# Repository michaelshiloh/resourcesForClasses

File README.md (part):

# General Resources for Classes

## Priorities (learned the hard way)

1. What is the minimum that you need to get done? Get that working first.
That way, if it's difficult you have more time to fix it, and if
it's impossible, you have more time to change your concept.  
1.1. If this is for a class, what's most of the grade?
1.1. If this is for yourself, what's the minimum you would need to feel proud?
1. In my experience, 
the mechanical things are the most difficult to get working, because usually
most students have the least amount of experience with this.
Get the mechanical parts work at least well enough before involving the
Arduino and programming.
1.1. If your robot is to be mobile, 
I would first get the mobility part working
1.1. If your robot has any other moving parts 
	(arms, tentacles, alien appendages, robot grippers) 
	I would try to get at least one of them working. 
1. The guiding principle is to do the things that you have the
least amount of experience with first And always leave the aesthetic stuff
until the very end. It doesn't matter if it looks like a jumble of junk, as
long as it works.  
1.1. One exception to the aesthetics is the wiring. As you've
probably discovered, a big mess of wires is very hard to debug, so spending
time to make the wires tidy can save you a lot of time later when things don't
work.

## Wisdom

1. MY GUIDING PRINCIPLES AFTER 20 YEARS OF PROGRAMMING
Medium
Alex Ewerlöf wrote an excellent article about his principles for working with software that I found could also apply to working on mechanical and electrical systems.

## Smoothing Readings from Noisy Sensors using Filters

1. Running average, built-in example in Arduino (File -> Examples -> Analog ->
Smoothing) [tutorial](https://www.arduino.cc/en/pmwiki.php?n=Tutorial/Smoothing)

1. [Another](https://maker.pro/arduino/tutorial/how-to-clean-up-noisy-sensor-data-with-a-moving-average-filter)
explanation of the running average filter

1. Great [discussion](https://www.megunolink.com/articles/coding/3-methods-filter-noisy-arduino-measurements/) and comparison
	of three smoothing methods: basic average, running average, and an
	exponential filter. The running average is the same as above. The
	exponential filter can be used by installing the *Megunolink* library
	(Sketch -> Include Library -> Manage Libraries, search for *Megunolink*) 

1. Many other filters are available through the library manager. I have not
	 tested these.

**Notes**
- While the examples above often refer to analog sensors, these methods
can be applied to all sensors (e.g. the ultrasonic distance measuring sensor)
- For beginners, I would recommend a basic average or a running average 
	- Basic average is faster to respond, but isn't quite as smooth as a running average.
	- In both cases, you will need to experiment with how many samples to take.  
		- A few samples responds quickly but won't be as smooth 
		- Many samples smooths well but won't respond quickly.  
	- You will have balance how much delay you can
tolerate vs. how smooth you need the result. Usually it's best to do this by
experimentation.

## Fabrication

1. Always design easy access for repair or modification. Never put items on
	 top of one another. Assume you will need easy access to each component.
	 Make access doors big so that you can easily put your hands in or bring
	 components out. Make holes for wires big enough that you can get the
	 connector through as well.
1. Make any enclosures at least twice as big as you think you'll need. Until
	 you're extremely experienced, you will underestimate how much room you'll
	 need and forget things like wires, which take up lots of space
1. Make wires longer than necessary, at least long enough that you can remove
	 a module and work on it comfortably (e.g. placing it face down on a
	 surface, not having to hold it at an uncomfortable angle)
1. Always use stranded wire between modules or between components and boards.
	 Solid wire can only be used when both ends are soldered to the same board.
1. Be consistent with colors: red for +5V (or whatever the dominant voltage
	 is), black wires for ground.
1. Don't have wires traverse empty space. Anchor wires to walls or other
	 support structures. Use zipties to bundle them neatly. 
1. Whenever possible, once you have finished the prototype transfer your
	 circuit from the solderless breadboard to a soldered board such as a
	 prototyping shield. Abolish all jumpers cables and instead solder
	 extensions as necessary. Use heat-shrink tubing on all solder joints to
	 prevent short circuits.

## Theory and critique
1. [Robotic Creatures](doc/roboticCreatures2010Ghedini.pdf)
1. [Catalog](doc/moma_catalogue_machine_art.pdf)
 from Machine Art exhibit, Museum of Modern Art, 1934 

### Art Critique: Examples and guides
1. [Beginner’s Guide to Writing an Art
   Critique](https://acousticpaint.wordpress.com/2018/07/31/beginners-guide-to-writing-an-art-critique/)
   Uses the foundational Feldman Method of art criticism.
   Somewhat beginner oriented. 
1. [How to: critique artwork like a
   pro](https://www.twistedtextiles.com/how-to-critique-artwork-like-a-pro/)
   As above
1. [Teaching Students to Critique](https://www.kennedy-center.org/education/resources-for-educators/classroom-resources/articles-and-how-tos/articles/educators/critique--feedback/teaching-students-to-critique/)
   As above
1. [How to Write an Art Critique: Examples &
   Strategies](https://custom-writing.org/blog/art-critique-writing)
   As above
1. [7 Art Critique Examples to Make You a Better Analyst
   (2025)](https://as.wiktoriaflorek.com/art-critique-examples/) describes 7
   different approaches to art criticism, all but one more advanced than the
   Feldman method. I found this the most useful because
   I could choose the approach that seems the most relevant to the situation
   and/or the artwork.
1. [Art Critique Example: The Persistence of Memory by Salvador
   Dali](https://hannahaafecak12.weebly.com/art-critique-example.html)
1. [Art Critique Example: The Weeping Woman by Pablo
   Picasso](https://16julianas.weebly.com/art-critique-example.html)

### Artist Statements
1. :
1. [8 Artist Statements We Love](https://www.theartleague.org/blog/2015/08/24/8-artist-statements-we-love/) this one starts with a Calvin and Hobbes cartoon so it's already a winner in my book
1. Reddit thread with [very useful advice from someone who covers art
   galleries](https://www.reddit.com/r/ContemporaryArt/comments/1emelpj/what_are_some_good_well_written_artist/)
1. Another Reddit thread with [useful
   advice](https://www.reddit.com/r/ContemporaryArt/comments/1dog1a4/the_artists_statement/)
1. [How To Write An Artist Statement, With
   Examples](https://www.stephaniescott.art/brushwork/2024/11/19/how-to-write-an-artist-statement)
   by someone who offers artist statement editing professionally
1. [Example Artist
   Statements](https://www.liverpoolmuseums.org.uk/example-artist-statements)
   from a museum so it must be good (I guess)
1. A whole bunch of [resources on writing artist
   statements](https://guides.ecuad.ca/professionalpractice/writing) with
   links to yet more examples
1. [Sample Artist Statements/Bios](https://www.gyst-ink.com/sample-artist-statements) from the resource above, because they
   seem really good

### Examples of well researched and well written papers about art
1. [Art of Interaction: A Theoretical Examination of Carsten Höller’s Test
   Site](https://www.tate.org.uk/research/tate-papers/15/art-of-interaction-a-theoretical-examination-of-carsten-holler-test-site)

## Inspiration: Artists, Movies, Projects, etc.

### Machine inspiration
- [DIY wire wrapping
- [Ghibli
	Clock](https://www.atlasobscura.com/places/the-giant-ghibli-clock-tokyo-japan)
	also [here](https://www.youtube.com/watch?v=R6nT8IEbaJM)
  machine](https://www.youtube.com/watch?v=3QL1QaIwMwk&t=482s)
- [Astronomical Clock Strasbourg
- [Fortnum & Mason store clock](https://www.youtube.com/watch?v=T7dWeTyexEg)
	Cathedral](https://www.youtube.com/watch?v=lKgZB3P45Kw)
- Series of 15 videos on [Mechanical
	Principles](https://www.youtube.com/watch?v=-42Z-_Kq0QU&list=PLq_UHnXWA4jI_gSAW9rvOr-I5Spqi3i_H)

1.  Drawing Machines
	1. [1](https://www.raspberrypi.org/blog/hanging-wall-plotter/)    
	1. [2](https://www.youtube.com/watch?v=T0jwdrgVBBc)    
	1. [3](http://www.homofaciens.de/technics-machines-v-plotter_en.htm)  
	1. [4](https://www.pinterest.com/pin/516014069788859472/)  
	1. [5](http://www.instructables.com/id/CNC-HANGING-PLOTTER/)  
	1. [6](http://patriciogonzalezvivo.com/2014/vPlotter/)  
	1. [7](http://www.instructables.com/id/Polargraph-Drawing-Machine/)  
	1. [8](https://www.thingiverse.com/thing:12557)  
	1. [9](https://www.thingiverse.com/thing:12403)  
	1. [10](http://makerblock.com/2013/03/a-study-of-drawing-robot-pen-holders-and-design-considerations/)  
	1. [11](https://www.kickstarter.com/projects/1765367532/duograph-drawing-machine?ref=nav_search)  
	1. [12](http://www.thisiscolossal.com/2016/03/cycloid-drawing-machine/)  
	1. The Machine As Artist, an
		 [Introduction](doc/theMachineAsArtistIntroduction.pdf)
  
1. Marble Machines
	1. [1](https://www.youtube.com/user/denha)  
	1. [2](https://tinkerlog.com/)  
	1. [3](https://www.youtube.com/watch?v=3OGyLHu24rk)

1. Didi Vardi's Wonderful Mechamisms
	1. [Binary Counter with old computer parts](media/binaryCounterDidiVardi.wmv)
	1. [Machine Animating late 19th century and early 20th century hand
		 tools](media/oldToolsMachineDidiVardi.wmv)

1. Musical Machines
	1. Carlos Guedes' wonderful [Phobos, Orquestra Robótica
	Disfuncional[(https://vimeo.com/235763130)
	4. Sudhu Tewari's [Yasmin Electro Mechanical 
	Sequencer](https://www.youtube.com/watch?v=MjNB3nKPMb8)
	1. Solenoid tapping wine glasses by [Lilliana Matta](https://vimeo.com/202356514) password
		 2424

1. List of [inspirational movies](http://eat.cca.edu) collected by [Barney
Haynes](http://www.ultrafuzz.net/) (also
[here](https://vimeo.com/barneyhaynes)) and shown at his Interface classes. In
particular

1. Inspirational videos collected by [J.D.
Zamfirescu](https://github.com/zamfi)  
	1. Basic robots  
		1. [Tree-climbing robot](http://www.youtube.com/watch?v=zkpH1BjD6Wc)  
		1. [Self-balancing robot](http://www.youtube.com/watch?v=Tw9Jr-SPL0Y)  
		1. [Insect robot](http://www.youtube.com/watch?v=tOsNXg2vAd4#t=120)  
		1. [Treadbot](http://www.youtube.com/watch?v=YblSltHDbIU)  
		1. [Velociraptor robot](http://www.youtube.com/watch?v=lPEg83vF_Tw)  
	1. Installations  
		1. [The Bay Lights](http://thebaylights.org/)  
		1. [Murmur Wall](http://www.future-cities-lab.net/projects/#/murmurwall/)  
		1. [Floating Couch](http://vimeo.com/72826106)  
		1. [Wooden Segment Mirror](https://www.youtube.com/watch?v=BZysu9QcceM#t=36)  
		1. [Generative design](https://www.youtube.com/watch?v=pNkz8wEJljc)  
	1. Art & Music bots  
		1. [Textile weaving](https://vimeo.com/71044541)  
		1. [ReacTable](https://www.youtube.com/user/marcosalonso)  
		1. [Projection mapping](https://www.youtube.com/watch?v=czuhNcNU6qU)  
		1. [Laser harp](http://www.youtube.com/watch?v=sLVXmsbVwUs#t=20)  
		1. [Cubli: Floating Cube](https://www.youtube.com/watch?v=n_6p-1J551Y)  
		1. [Arc-o-matic](http://vimeo.com/57082262#at=130)  
		1. [Robo Faber](http://vimeo.com/78771257)  
		1. [Eggbot](https://www.youtube.com/watch?v=w4cdbV2oaEc)  
	1. Drink-makers  
		1. [Textspresso](http://www.youtube.com/watch?v=kx9D74t7GD8#t=89)  
		1. [The Inebriator](http://www.youtube.com/watch?v=WqY7fchs7H0)  
	1. Computer Numerical Control (CNC)  
		1. [Shapoko / tinyg](http://www.youtube.com/watch?v=pCC1GXnYfFI#t=11)  
		1. [Makerbot Replicator](http://www.youtube.com/watch?v=NAbiAzYhTOQ)  
	1. Vacuuming  
		1. [Roomba](https://www.youtube.com/watch?v=0DNkbZvVYvc)  

2. [Golan Levin: Art that looks back at
you](https://www.youtube.com/watch?v=1G0MzlfMPuM)

3. [Drawdio](https://www.youtube.com/watch?v=PV_w38ldZaE)

4. Other Projects  
	1. Alex Markova's [fortune wheel](http://intro17fall.nyuad.im/2017/10/09/homework-due-october-9/)  
	1. Claire Neel's [reactive eye](https://youtu.be/lYERKTf5YtI)  
	1. Ji Young Kim's [map and national anthems](https://youtu.be/JknAOpjAkmQ)
	1. May Baho's [campfire](http://intro17fall.nyuad.im/wp-content/uploads/2017/12/IMG_2544.jpg)  

### Solderless Breadboards

1. [How to Use a Breadboard](https://learn.sparkfun.com/tutorials/how-to-use-a-breadboard) tutorial by Sparkfun
1. [Setting Up a Breadboard](https://itp.nyu.edu/physcomp/labs/labs-electronics/breadboard/) lab at NYU ITP

### Basic Electronics

1. [Basic Electronics](https://learn.sparkfun.com/tutorials/voltage-current-resistance-and-ohms-law) tutorial by Sparkfun
1. [Electricity: the Basics](https://itp.nyu.edu/physcomp/lessons/electronics/electricity-the-basics/) tutorial at NYU ITP

### Data Visualization Examples

1. [Ben Fry](http://benfry.com/allstreets/)

2. [Aaron Koblin](http://www.aaronkoblin.com/project/flight-patterns/)

3. Jer Thorp

	3.1. [Just
Landed](http://blog.blprnt.com/blog/blprnt/just-landed-processing-twitter-metacarta-hidden-data)

	3.2. [another](http://nytlabs.com/projects/cascade.html)

	3.3. [nytimes top coverage and
connections](https://www.flickr.com/photos/blprnt/sets/72157614008027965/with/3288898519/)

4. [Nicholas Feltron](http://feltron.com/FAR14.html)

### Mechanical or Primarily Mechanical

1. [Survival Research Labs](http://www.srl.org) Machine or industrial art

2. [Matt Heckert](http://www.mattheckert.com/)
Machine and kinetic art, machine sound art, and creator of many early SRL
machines

3. [Carl Pisaturo](http://carlpisaturo.com/index.html)
Artist, master machinist, and inventor, Carl documents his process in detail
for great learning opportunities. Great examples of complex motions via cables

4. [North Pitney](http://www.northpitney.com/)
North Pitney’s amazing [reconfigurable maze](http://www.northpitney.com/works/maze/maze.html) is one of my favorite examples of kinetic art.

5. Arthur Ganson
makes amazing sculptures using wire gears and mechanisms
[Making wire gears](http://www.youtube.com/watch?v=f0UNz-ayzrE)
Sample piece: [Meditation #1](http://www.youtube.com/watch?v=kY2Df78faiE)
Search youTube for many other videos of his work

6. Daniel Rozinin
[Wooden
mirror](http://www.designboom.com/weblog/read.php?CATEGORY_PK=&TOPIC_PK=2897) 
in which over 800 small blocks of wood
are individually rotated slightly to display an image of what the camera
captures

7. [Theo Jansen](http://www.strandbeest.com/)
Theo Jansen creates new forms of life using plastic tubing as the basic
building material. Wind is their "food", and their "stomach" is made of recycled
plastic bottles.
Theo’s [The art of creating
creatures](http://www.youtube.com/watch?v=b694exl_oZo) 
presentation at TED in 2006 includes
a wonderful video of his work and a live demonstration of portions of his
mechanisms. Search youTube for many other videos of his work

8. [Del’s Beautiful New Wooden
Machine](http://www.youtube.com/watch?v=u7ziwuIpnVY)
An intricate hand-cranked machine demonstrating many types of simple
mechanisms: cranks, gears, chains, sprockets, offset gears to change speed,
escapements, conversion of rotary motion to linear motion. Thanks to Tristan
for bringing this to my attention.

## Basic Arduino Resources from Arduino

1. Getting Started with Arduino / Genuino Uno
    [tutorial](https://www.arduino.cc/en/Guide/ArduinoUno)

1. Blink [tutorial](http://arduino.cc/en/Tutorial/Blink)

1. DigitalReadSerial [tutorial](http://arduino.cc/en/Tutorial/DigitalReadSerial)

1. AnalogReadSerial [tutorial](http://arduino.cc/en/Tutorial/AnalogReadSerial)

2. Fade [tutorial](http://arduino.cc/en/Tutorial/Fade)
shows how to use the `analogWrite()` function

## Basic Arduino Resources from Other Sources

1. Arduino basics: Intro through Lesson 3 of Adafruit's Arduino [tutorial](http://www.ladyada.net/learn/arduino/index.html)

1. [Arduino in a Nutshell](http://hci.rwth-aachen.de/arduino)

1. Photoresistor
[Instructables](http://www.instructables.com/id/How-to-Use-a-Light-Dependent-Resistor-LDR/)

## Sparkfun Inventor's Kit Resources

1. [Introduction](https://learn.sparkfun.com/tutorials/sik-experiment-guide-for-arduino---v32/introduction-sik-arduino-uno)
to the Sparkfun Inventor's Kit for Arduino Experimenter's Guide

1. [Experiment 1: Blinking an LED](
https://learn.sparkfun.com/tutorials/sik-experiment-guide-for-arduino---v32/experiment-1-blinking-an-led)
in the Sparkfun Inventor's Kit for Arduino Experimenter's Guide

1. [Experiment 2: Reading a
Potentiometer](https://learn.sparkfun.com/tutorials/sik-experiment-guide-for-arduino---v32/experiment-2-reading-a-potentiometer)
in the Sparkfun Inventor's Kit for Arduino Experimenter's Guide

## Blink Without Delay Resources

1. [Tutorial](https://www.arduino.cc/en/Tutorial/BlinkWithoutDelay)
to Blink Without Delay on the official Arduino website

1. [Another](https://www.baldengineer.com/millis-tutorial.html) 
explanation of Blink Without Delay recommended by a student

1. The same student recommends that in order to understand Blink Without
Delay, it is wise to first understand
[millis()](https://www.arduino.cc/en/Reference/Millis)

1. Very detailed line-by-line
[explanation](https://www.baldengineer.com/blink-without-delay-explained.html)
of Blink Without Delay, with links
to explanations of related concepts every step of the way.

2. A detailed
[explanation](https://programmingelectronics.com/tutorial-16-blink-an-led-without-using-the-delay-function-old-version/) of Blink Without Delay. 
I don't like the way he does the circuit, but his explanation is good.

## Arduino Multitasking Resources

1. Excellent Adafruit Multitasking
[Tutorial](https://learn.adafruit.com/multi-tasking-the-arduino-part-1?view=all)
(highly recommended)

1. Play a melody and blink an LED
without using `delay()`:
[toneMelodyAndBlinkWithoutDelay](https://github.com/michaelshiloh/toneMelodyAndBlinkWithoutDelay)

1. Flicker (i.e simulate a candle) multiple LEDs
without using `delay()`:
[flickerMultipleNoDelay](https://github.com/michaelshiloh/resourcesForClasses/blob/master/src/arduinoSketches/flickerMultipleNoDelay/flickerMultipleNoDelay.ino)

## State, state machines, and state change detection (edge detection)

1. [State Change Detection](https://www.arduino.cc/en/Tutorial/StateChangeDetection)

1. A formal State Machine is called a *Finite State Machine* (FSM). Although
	 you can often get away with being less formal, here is a nice
	 [tutorial](https://www.instructables.com/Finite-State-Machine-on-an-Arduino/)
	 on FSMs

2. Adafruit 
	[tutorial](http://www.ladyada.net/learn/arduino/lesson5.html)

3. Another 
	[edge detection tutorial](https://programmingelectronics.com/tutorial-18-state-change-detection-and-the-modulo-operator-old-version/)

## Arduino Tone Resources

1. Decent explanation
[here](https://programmingelectronics.com/an-easy-way-to-make-noise-with-arduino-using-tone/)

2. Using switches to control the tone
[here](http://arduino-tutorials.eu/creating-sounds-with-arduino-buzzer)

## Arduino Sensors Resources

1. Adafruit [guide](http://www.ladyada.net/learn/sensors/) to sensors

## Shift Register resources

1. Adafruit Shift Register
[tutorial](https://learn.adafruit.com/adafruit-arduino-lesson-4-eight-leds/the-74hc595-shift-register)

1. Arduino Shift Register
[tutorial](https://www.arduino.cc/en/Tutorial/ShiftOut)

2. Electronics Tutorials
Shift Register
[tutorial](https://www.electronics-tutorials.ws/sequential/seq_5.html)

1. Sparkfun 
Shift Register
[tutorial](https://learn.sparkfun.com/tutorials/shift-registers)

## Communication resources

1. Sparkfun Serial Communication tutorial
[here](https://learn.sparkfun.com/tutorials/serial-communication)

## Miscellaneous Electronic resources

1. Sparkfun 
Logic Level 
[tutorial](https://learn.sparkfun.com/tutorials/logic-levels)

## Mechatronic Resources

1. [Walking
	 boots](https://www.mutualart.com/Artwork/THESE-BOOTS-ARE-MADE-FOR-WALKING/8DF4DB74D0B36CA0)

1. YouTube [playlist](https://www.youtube.com/playlist?list=PLLFpXNanTP9X6lHrX9qoJroqGAQRDDvV9)
of antique (and ancient) counting and calculating devices with a huge variety of mechanisms 

1. Ken Shirriff
	 [details](https://www.righto.com/2023/01/inside-globus-ink-mechanical-navigation.html)
the intricate mechanical systems of the Globus INK – a gorgeous navigation system for soviet spacecraft. It features a rotating globe inside a metal housing, and let Soyuz cosmonauts see their position above Earth.

1. Simple [descriptions](http://www.mechanical-toys.com/mechanisums.htm) of
the 6 basic mechanisms

1. [Table of Mechanicks
	 [sic]](media/Table_of_Mechanicks_Cyclopaedia_Volume_2.jpg)

1. Great book describing how to build [Mechanisms](doc/machinations-mechanisms.pdf)

1. How to build a [Crank and
	 Slider](https://www.wikihow.com/Build-a-Crank-and-Slider-Mechanism) 
	 mechanism

1. [Gear generator](http://www.geargenerator.com)

1. Pages 272-281 in "Physical Computing: Sensing and Controlling the
Physical World with Computers" by Igoe/O'Sullivan

1. [How To Design And Make Automata](doc/howToDesignAndMakeAutomata_RobertAdams.pdf) by Robert Adams

1. [How To Design And Make Simple Automata](doc/howToDesignAndMakeSimpleAutomata_RobertAdams.pdf) by Robert Adams (I think this is a different version of the same book above)

1. Different shaped cams provide [different types of reciprocating motion](https://static.fratello.com/2021/08/camupdate1.gif)

1. A nice [overview](https://makezine.com/projects/make-your-own-gears/) of
making your own gears. Don't worry about the specifics (Inkscape etc.) 
but get the general concept which can be achieved in many different 
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
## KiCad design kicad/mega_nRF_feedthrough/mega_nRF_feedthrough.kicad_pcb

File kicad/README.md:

Some PCBs I have designed to help with my classes and other projects:
- ArduinoShieldHobbyRCAndMotorControl: Holes for 6 wires to connect
  to an L298 (or similary) dual H-bridge motor driver, and six connectors
  suitable for a hobby RC receiver. 
  Used in [Performing
  Robots](https://github.com/michaelshiloh/PerformingRobots)
  but could be useful to
  anyone connecting an Arduino Uno to a hobby RC receiver or an L298 dual
  H-bridge motor driver.
- IC_sockets/16PinSocketAPC: breakout board for a 14 pin DIP, with silkscreen
  markings aimed at making at Atari Punk Console. I'll add a link to the full
  instructions when I find them.
- nRF_servo_Mega: Arduino Mega shield for mounting nRF24L01 and attaching six
  servo motors or NeoPixels strings with separate power supply
  Used in [Performing
  Robots](https://github.com/michaelshiloh/PerformingRobots).
  but could be useful to
  anyone connecting an Arduino Mega to an nRF24L01
  or servo motors/NeoPixel strings.
- l298Interface: rather than using horrible jumper cables, this board fits
  directly to the 6 control pins on an L298 dual H-bridge motor driver and
  provides holes for soldering wires to the
  ArduinoShieldHobbyRCAndMotorControl above. Also includes a 3 position ground
  tie point to avoid having to jam 2 wires into one of the screw terminals.
  Used in [Performing
  Robots](https://github.com/michaelshiloh/PerformingRobots) but could be
  generically useful.
- Arduino_Shield_RC_Controller: Obsolete. Do not use.
- Arduino_Shield_RC_Controller_v2: Wireless remote control panel using the
  nRF24L01.
  Used in [Performing
  Robots](https://github.com/michaelshiloh/PerformingRobots)
  but could be useful to
  anyone wanting a wireless remote control panel using an nRF24L01.
- motorMatrixAdapter: starting point for my matrix-of-motors project
- ArduinoShieldServoMotors: Arduino Uno shield for 9 servo motors or NeoPixel
  strands with separate power supply.
  Used in [Machine 
  Lab](https://github.com/michaelshiloh/MachineLab) 
  but could be useful to
  anyone connecting servo motors to an Arduino Uno
- nRFControlPanel: Obsolete. Do not use.

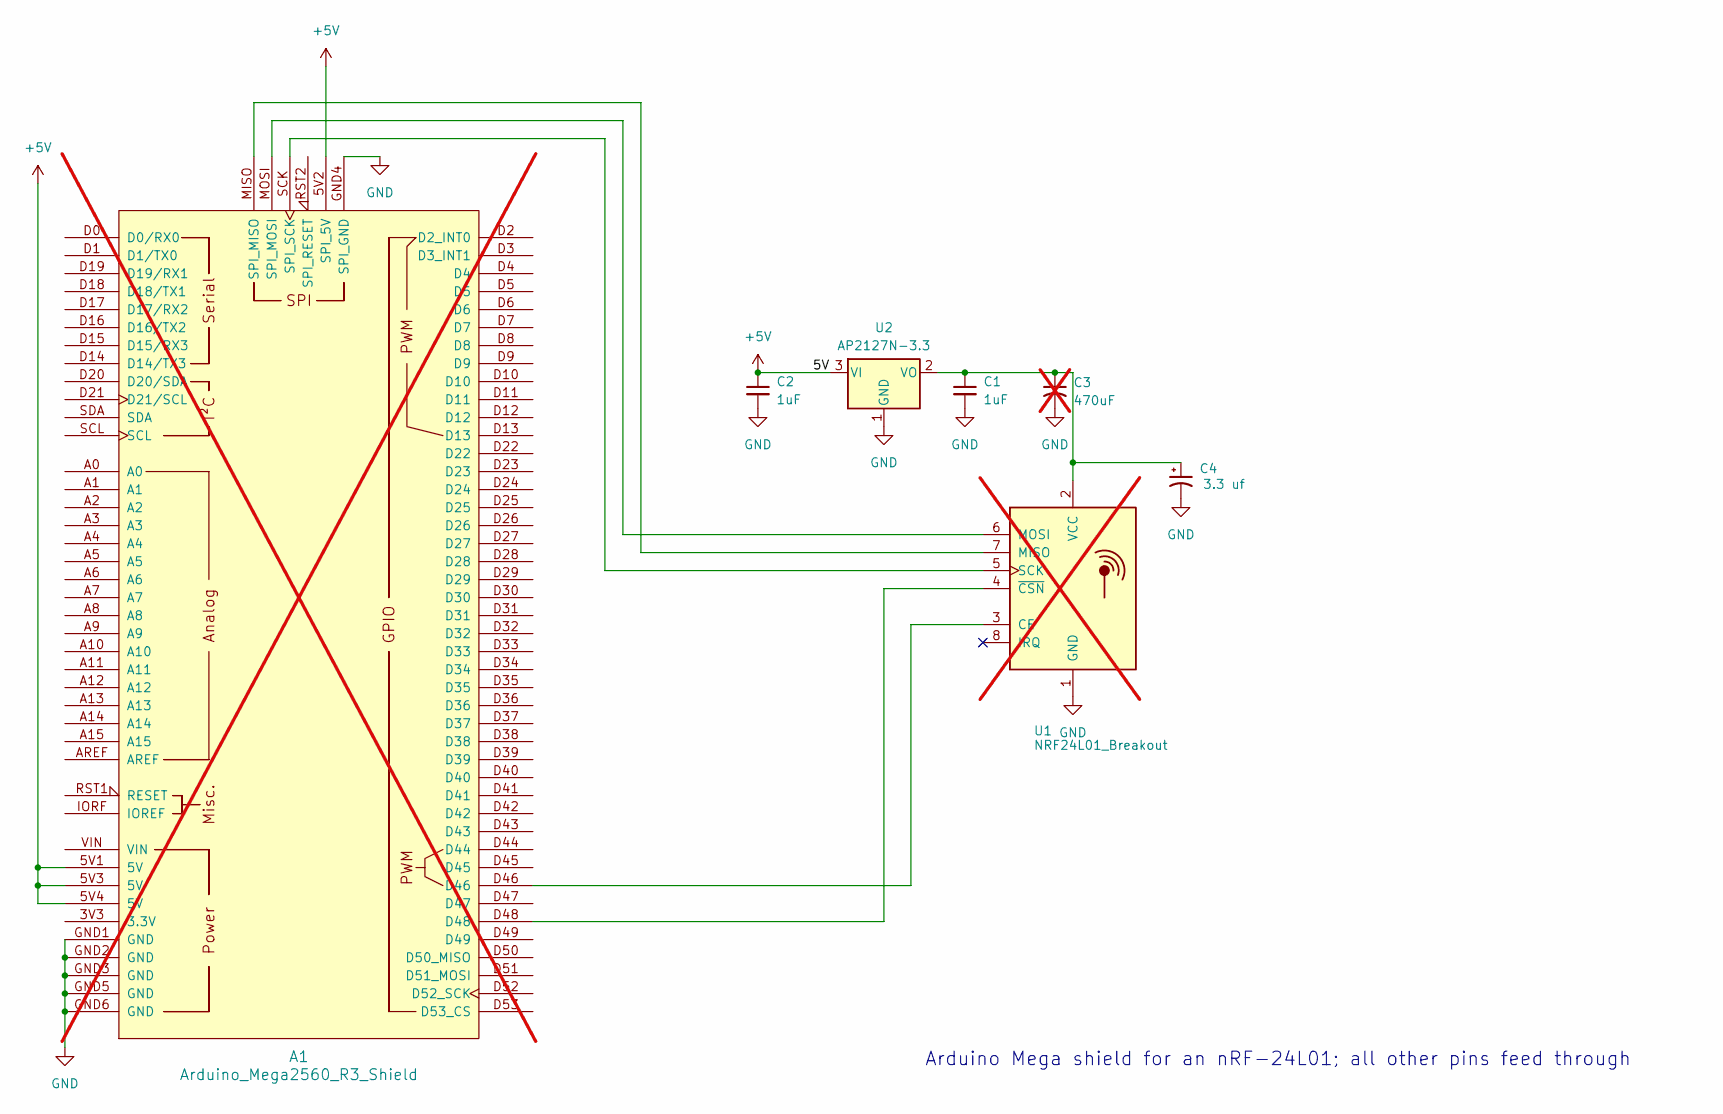
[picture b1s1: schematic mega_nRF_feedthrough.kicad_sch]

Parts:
A1: Arduino_Mega2560_R3_Shield; not fitted
C1: 1uF; C_0603_1608Metric; LCSC part # C1592
C2: 1uF; C_0603_1608Metric; LCSC Part # C1592
C3: 470uF; CP_Radial_D8.0mm_P3.50mm; not fitted
C4: 3.3 uf; CP_EIA-3216-18_Kemet-A_HandSolder; LCSC Part # C7184
U1: NRF24L01_Breakout; nRF24L01_Breakout; not fitted
U2: AP2127N-3.3; SOT-23

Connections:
+5V: A1.5V1 (5V), A1.5V2 (SPI_5V), A1.5V3 (5V), A1.5V4 (5V), C2.1, U2.3 (VI)
GND: A1.GND1 (GND), A1.GND2 (GND), A1.GND3 (GND), A1.GND4 (SPI_GND), A1.GND5 (GND), A1.GND6 (GND), C1.2, C2.2, C3.2, C4.2, U1.1 (GND), U2.1 (GND)
unnamed: A1.MISO (SPI_MISO), U1.7 (MISO)
unnamed: A1.MOSI (SPI_MOSI), U1.6 (MOSI)
unnamed: A1.SCK (SPI_SCK), U1.5 (SCK)
unnamed: A1.D46, U1.3 (CE)
unnamed: C1.1, C3.1, C4.1, U1.2 (VCC), U2.2 (VO)
unnamed: A1.D48, U1.4 (~CSN)

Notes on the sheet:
Arduino Mega shield for an nRF-24L01; all other pins feed through

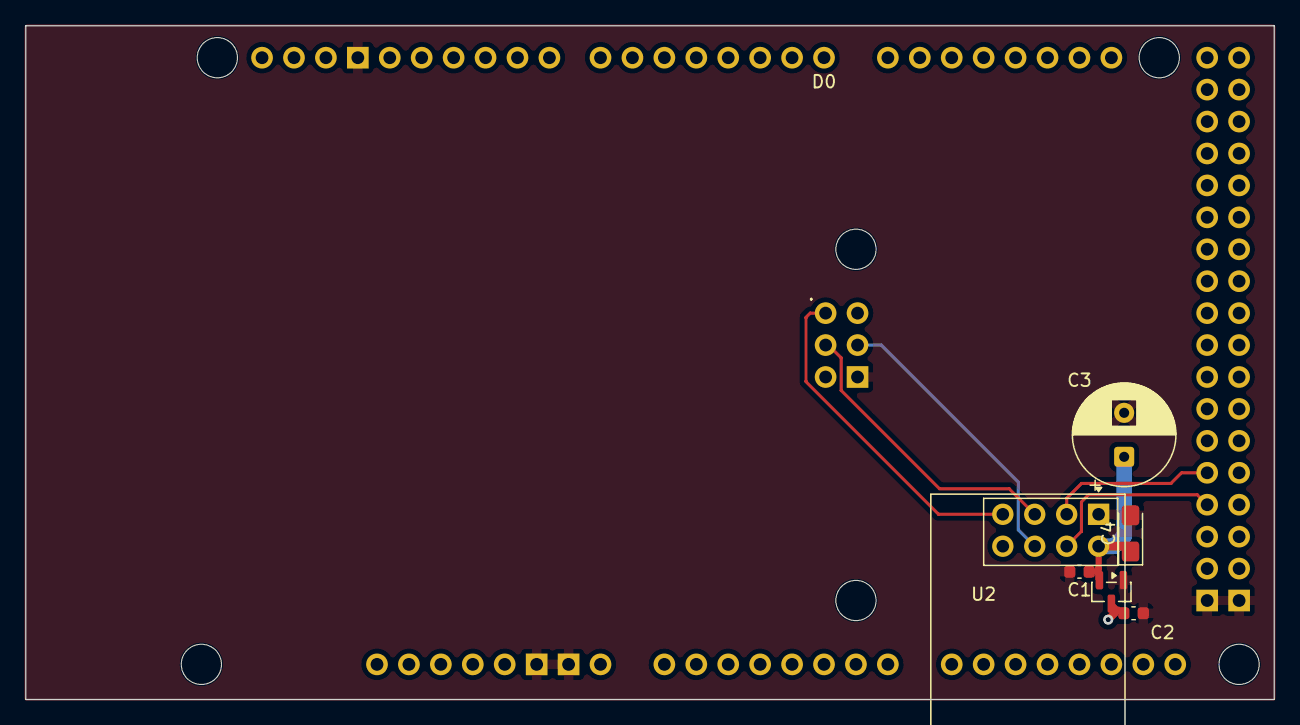
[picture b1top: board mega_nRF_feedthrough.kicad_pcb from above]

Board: 2 copper layers, 99.3 x 53.6 mm, 7 parts (0 on the bottom side), 8 nets.

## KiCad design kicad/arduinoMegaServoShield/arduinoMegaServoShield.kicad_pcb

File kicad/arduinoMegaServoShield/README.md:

### nRF_Servo_Mega

![](documentation/arduinoMegaServoShield.jpg
[PDF schematic](documentation/arduinoMegaServoShield.pdf)

Simple Arduino Mega shield which provides as many connections to servo motors
or other 3-pin devices (such as NeoPixels) with an independent +V supply

Be aware of pins which might be used for other purposes

Music Maker Shield

(why is the first column labled SPI?)
| SPI Signal Name | Description | Arduino Mega Pin |
| --- | --- | --- |
| MCS | VS1053 chip select pin | 7 |
| DCS | VS1053 data select pin | 6 |
| CCS | SD Card chip select pin | 4 |
| DREQ | VS1053 data request interrupt pin | 3 |

SPI

| SPI Signal Name | Arduino Mega Pin |
| --- | --- |
| CIPO | 50 |
| COPI | 51 |
| SCK | 52 |
| CS | 53 |

I2C (also known as Wire or 2Wire)

| I2C Signal Name | Arduino Mega Pin |
| --- | --- |
| SDA | 20 |
| SCL | 21 |

Serial 

| Serial Signal Name | Arduino Mega Pin |
| --- | --- |
| RX | 0 |
| TX | 1 |

#### Revisions

#### Assembly instructions
##### Assembly order
1. servo pins
1. Stacking headers
1. Screw terminal
1. ICSP header
1. 470 uFD caps

(Note that the order of the instructions and video below are slightly
different - I don't think it makes much of a difference.)

##### Assembly instructions
nRF Servo Mega Shield [video](https://youtu.be/EMkqwKK7xOQ)

1. Prepare many sets of header pins, each with 3 positions. 

    Insert into positions
   D16-D21.
   Solder one pin, straighten, and
   then solder the rest of the pins. You may find it easier to do one header
   at a time instead of trying to do all 6 at once like I did.
    
1. From the bag of feed-through headers, remove six 5 position headers and one
   10 position header. Return the rest to the bag.
    Solder one pin, straighten, then solder the rest. It is very important to
    get these to line up properly so don't solder the rest of the pins until
    the header is straight.
1. Install the feed through header that is two rows of 3 pins. **Note that
   this goes in the opposite direction i.e. the pins face up and the socket
   faces down**. Solder and straighten.
1. Install the 470 uFD electrolytic capacitor. 
    Note that this component **is polarized** so you have to install it in
    the right direction. The grey stripe must go into the hole with the white
    semicircle.
   Cut the excess leads right down to the solder. Discard the cut of portion
   so that it doesn't cause a short circuit
1. Install the screw terminal. Make sure that the openings face the edge of
   the board. Solder. These pins are quite thick and the hole is quite big, so
   keep feeding solder until the hole fills up.

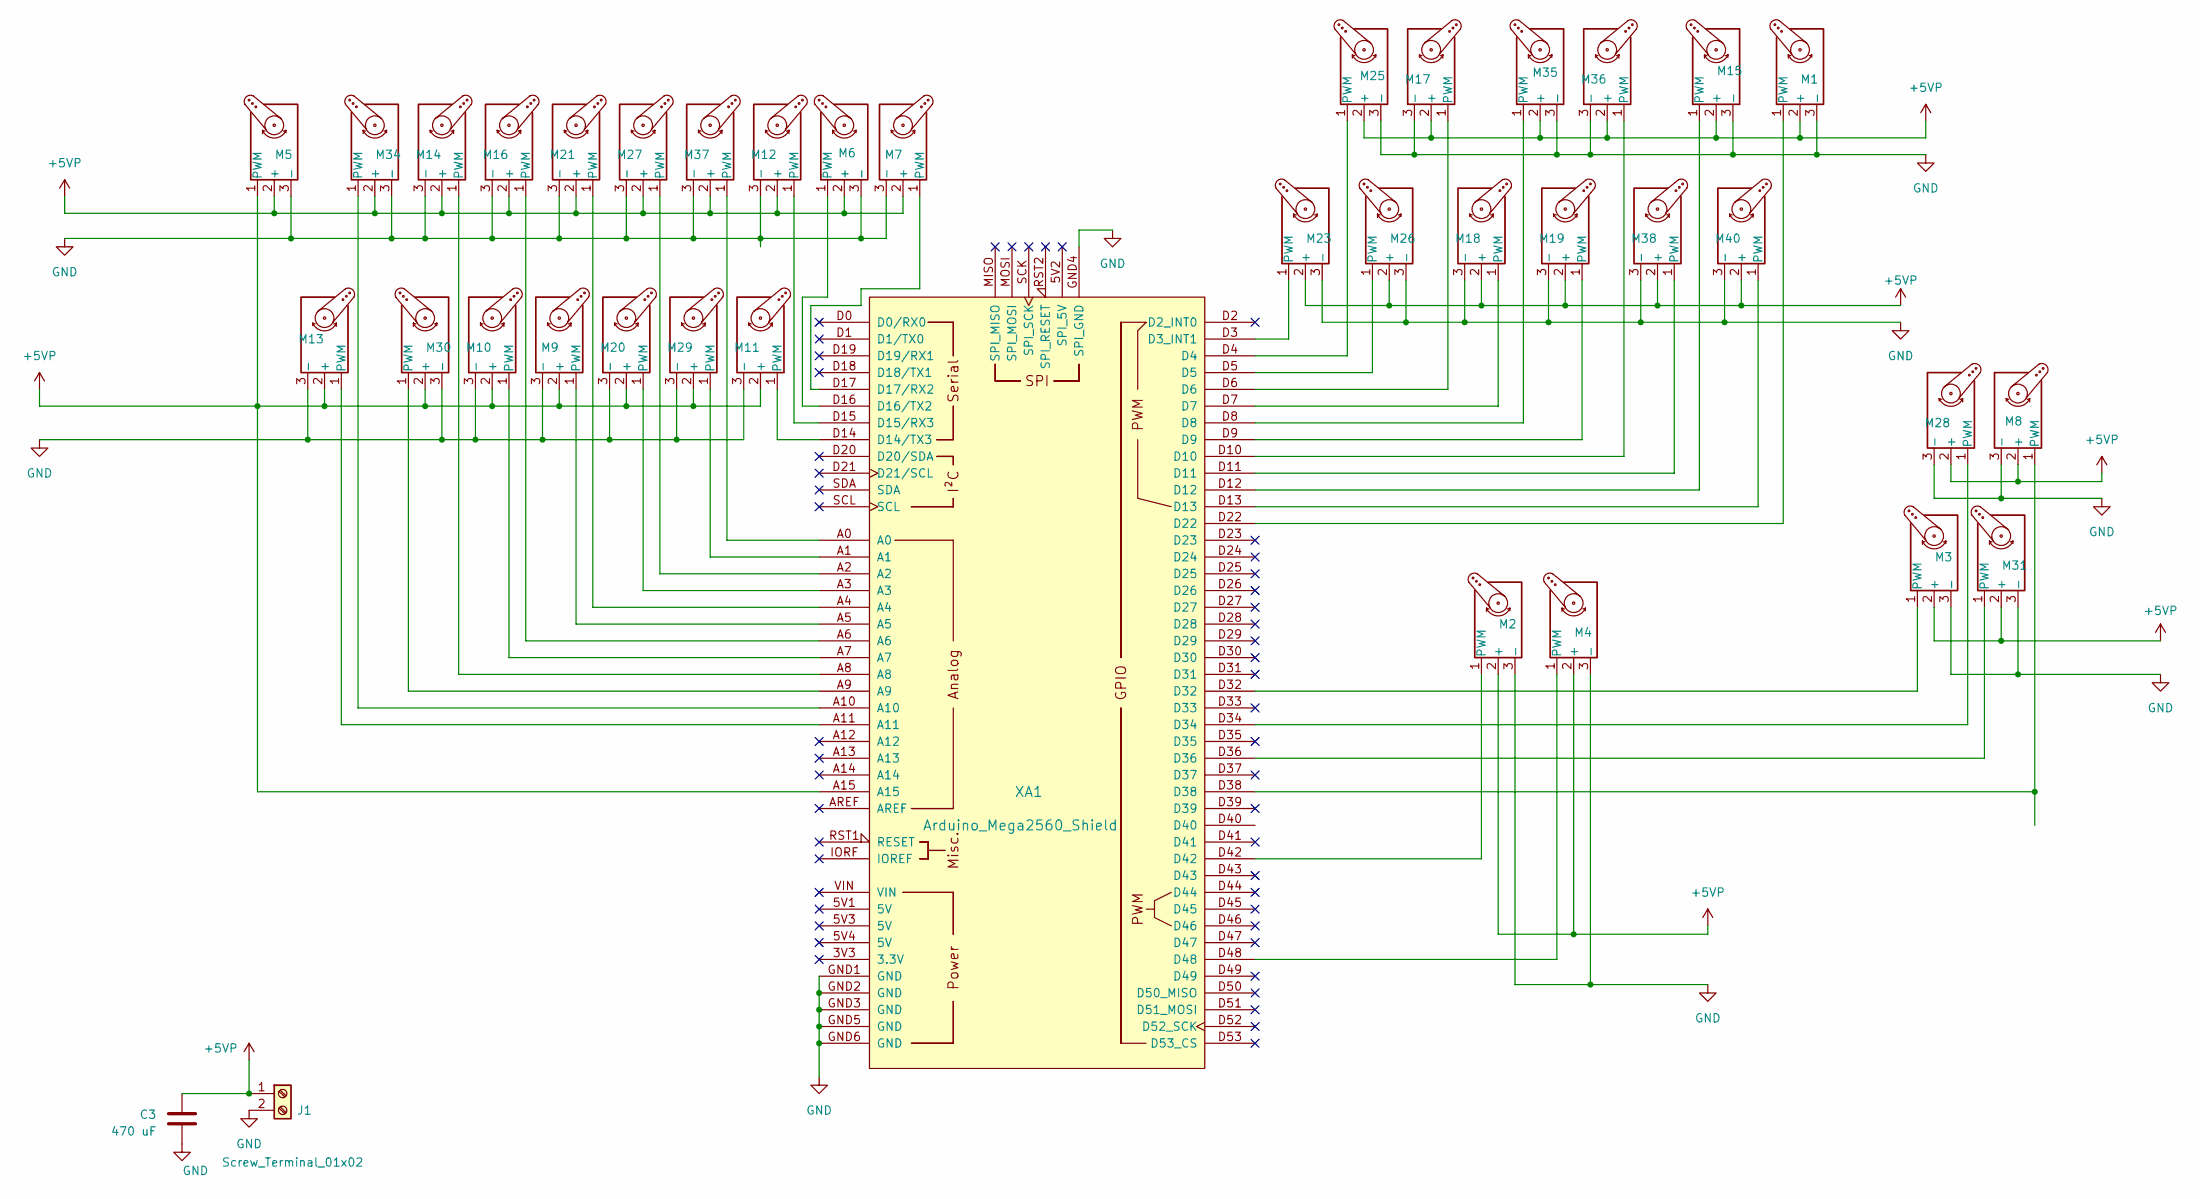
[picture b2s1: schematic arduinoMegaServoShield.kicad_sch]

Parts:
C3: 470 uF; CP_Radial_D10.0mm_P5.00mm
J1: Screw_Terminal_01x02; TerminalBlock_bornier-2_P5.08mm
M1, M2, M3, M4, M5, M6, M7, M8, M9, M10, M11, M12, M13, M14, M15, M16, M17, M18, M19, M20, M21, M23, M25, M26, M27, M28, M29, M30, M31, M34, M35, M36, M37, M38, M40: Motor_Servo; PinHeader_1x03_P2.54mm_Vertical
XA1: Arduino_Mega2560_Shield

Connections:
+5VP: C3.1, J1.1, M1.2 (+), M2.2 (+), M3.2 (+), M4.2 (+), M5.1 (PWM), M5.2 (+), M6.2 (+), M7.2 (+), M8.2 (+), M9.2 (+), M10.2 (+), M11.2 (+), M12.2 (+), M13.2 (+), M14.2 (+), M15.2 (+), M16.2 (+), M17.2 (+), M18.2 (+), M19.2 (+), M20.2 (+), M21.2 (+), M23.2 (+), M25.2 (+), M26.2 (+), M27.2 (+), M28.2 (+), M29.2 (+), M30.2 (+), M31.2 (+), M34.2 (+), M35.2 (+), M36.2 (+), M37.2 (+), M38.2 (+), M40.2 (+), XA1.A15
GND: C3.2, J1.2, M1.3 (-), M2.3 (-), M3.3 (-), M4.3 (-), M5.3 (-), M6.3 (-), M7.3 (-), M8.3 (-), M9.3 (-), M10.3 (-), M11.3 (-), M12.3 (-), M13.3 (-), M14.3 (-), M15.3 (-), M16.3 (-), M17.3 (-), M18.3 (-), M19.3 (-), M20.3 (-), M21.3 (-), M23.3 (-), M25.3 (-), M26.3 (-), M27.3 (-), M28.3 (-), M29.3 (-), M30.3 (-), M31.3 (-), M34.3 (-), M35.3 (-), M36.3 (-), M37.3 (-), M38.3 (-), M40.3 (-), XA1.GND1 (GND), XA1.GND2 (GND), XA1.GND3 (GND), XA1.GND4 (SPI_GND), XA1.GND5 (GND), XA1.GND6 (GND)
unnamed: M1.1 (PWM), XA1.D22
unnamed: M2.1 (PWM), XA1.D42
unnamed: M3.1 (PWM), XA1.D32
unnamed: M4.1 (PWM), XA1.D48
unnamed: M6.1 (PWM), XA1.D16 (D16/TX2)
unnamed: M7.1 (PWM), XA1.D17 (D17/RX2)
unnamed: M8.1 (PWM), XA1.D38
unnamed: M9.1 (PWM), XA1.A5
unnamed: M10.1 (PWM), XA1.A7
unnamed: M11.1 (PWM), XA1.D14 (D14/TX3)
unnamed: M12.1 (PWM), XA1.D15 (D15/RX3)
unnamed: M13.1 (PWM), XA1.A11
unnamed: M14.1 (PWM), XA1.A8
unnamed: M15.1 (PWM), XA1.D12
unnamed: M16.1 (PWM), XA1.A6
unnamed: M17.1 (PWM), XA1.D6
unnamed: M18.1 (PWM), XA1.D7
unnamed: M19.1 (PWM), XA1.D9
unnamed: M20.1 (PWM), XA1.A3
unnamed: M21.1 (PWM), XA1.A4
unnamed: M23.1 (PWM), XA1.D3 (D3_INT1)
unnamed: M25.1 (PWM), XA1.D4
unnamed: M26.1 (PWM), XA1.D5
unnamed: M27.1 (PWM), XA1.A2
unnamed: M28.1 (PWM), XA1.D34
unnamed: M29.1 (PWM), XA1.A1
unnamed: M30.1 (PWM), XA1.A9
unnamed: M31.1 (PWM), XA1.D36
unnamed: M34.1 (PWM), XA1.A10
unnamed: M35.1 (PWM), XA1.D8
unnamed: M36.1 (PWM), XA1.D10
unnamed: M37.1 (PWM), XA1.A0
unnamed: M38.1 (PWM), XA1.D11
unnamed: M40.1 (PWM), XA1.D13

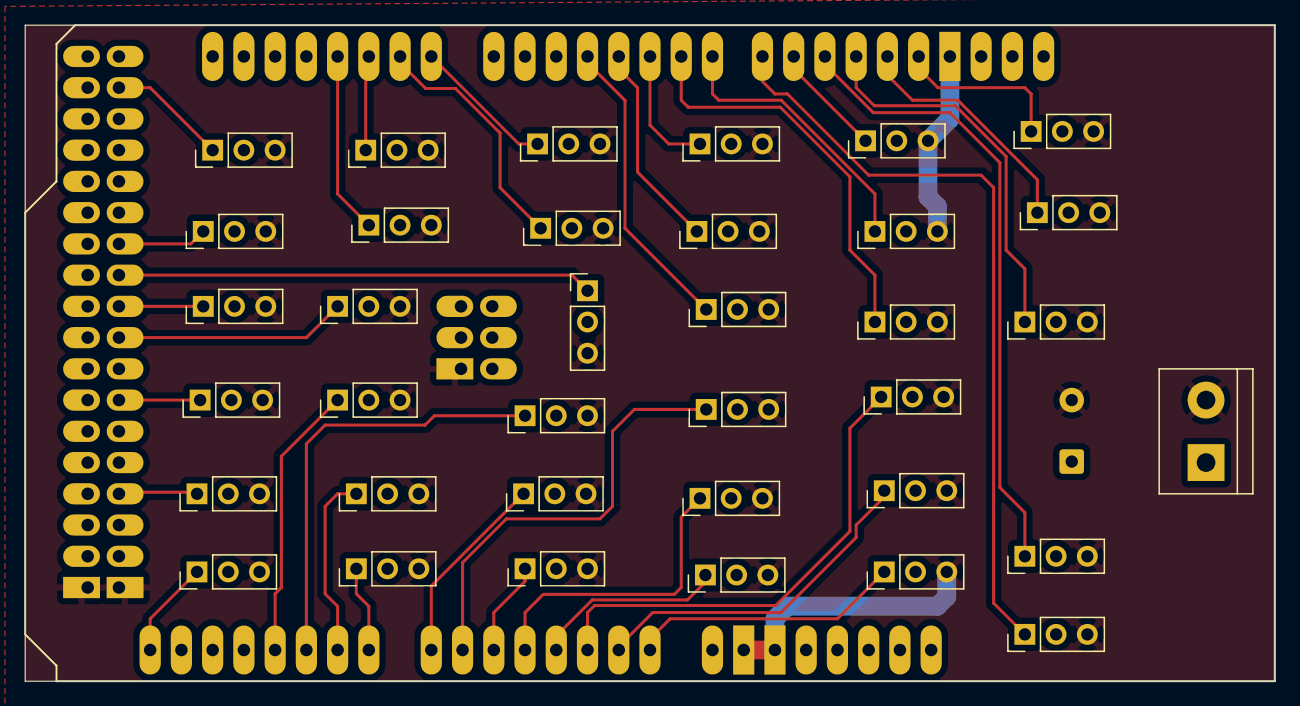
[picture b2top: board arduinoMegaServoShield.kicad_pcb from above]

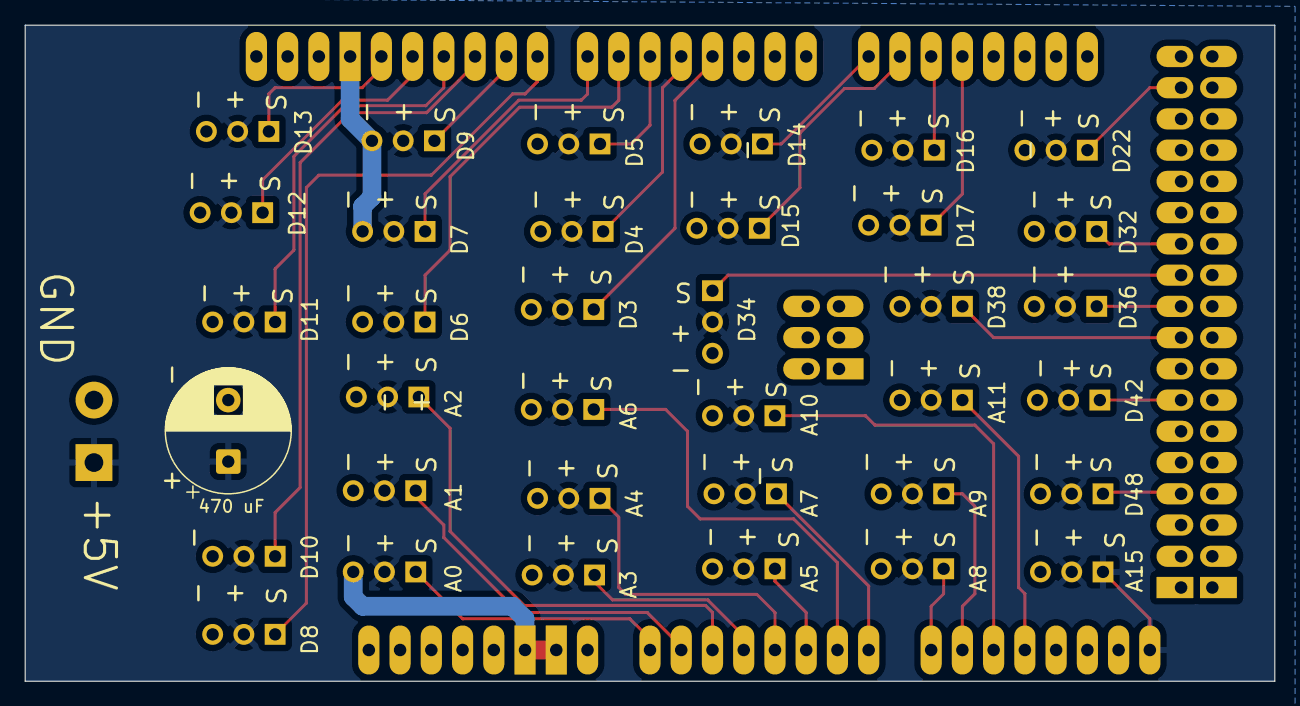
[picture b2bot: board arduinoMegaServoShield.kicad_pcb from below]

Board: 2 copper layers, 101.6 x 53.3 mm, 38 parts (2 on the bottom side), 36 nets.

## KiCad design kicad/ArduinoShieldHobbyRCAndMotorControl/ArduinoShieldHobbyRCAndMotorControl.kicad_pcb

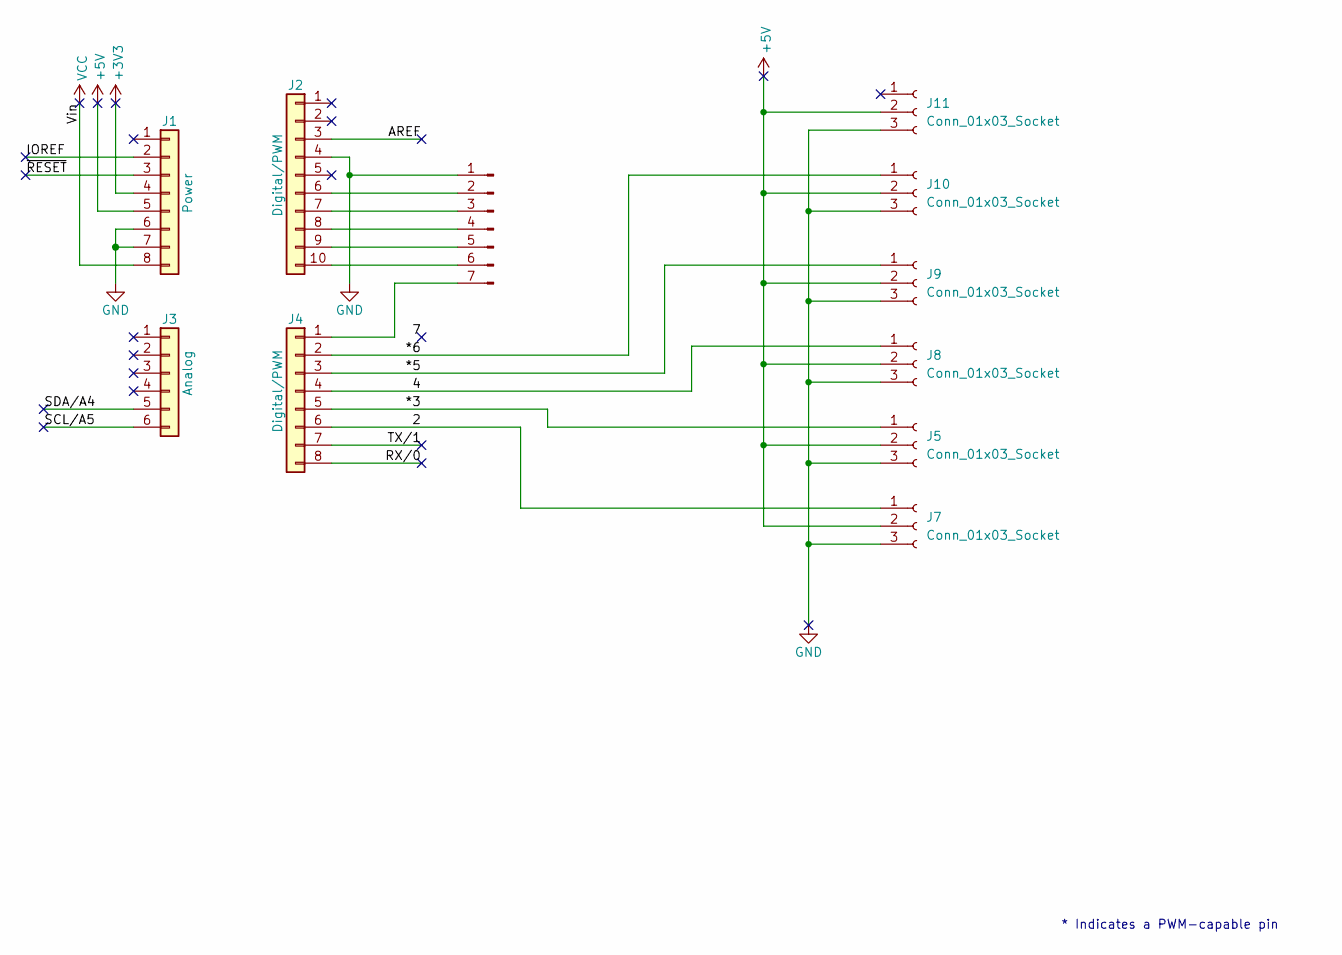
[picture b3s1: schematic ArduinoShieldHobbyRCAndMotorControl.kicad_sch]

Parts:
J1: Power; PinSocket_1x08_P2.54mm_Vertical
J2: Digital/PWM; PinSocket_1x10_P2.54mm_Vertical
J3: Analog; PinSocket_1x06_P2.54mm_Vertical
J4: Digital/PWM; PinSocket_1x08_P2.54mm_Vertical
J5, J7, J8, J9, J10, J11: Conn_01x03_Socket; PinSocket_1x03_P2.54mm_Vertical
J6: Conn_01x07_Pin; TerminalBlock_WAGO_236-107_1x07_P5.00mm_45Degree

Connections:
+3V3: J1.4
+5V: J1.5, J5.2, J7.2, J8.2, J9.2, J10.2, J11.2
/2: J4.6, J7.1
/4: J4.4, J8.1
/*3: J4.5, J5.1
/*5: J4.3, J9.1
/*6: J4.2, J10.1
/AREF: J2.3
/IOREF: J1.2
/RX/0: J4.8
/SCL/A5: J3.6
/SDA/A4: J3.5
/TX/1: J4.7
/~RESET: J1.3
GND: J1.6, J1.7, J2.4, J5.3, J6.1, J7.3, J8.3, J9.3, J10.3, J11.3
unnamed: J2.6, J6.2
unnamed: J2.7, J6.3
unnamed: J2.8, J6.4
unnamed: J2.9, J6.5
unnamed: J2.10, J6.6
unnamed: J4.1, J6.7
VCC: J1.8

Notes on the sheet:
* Indicates a PWM-capable pin

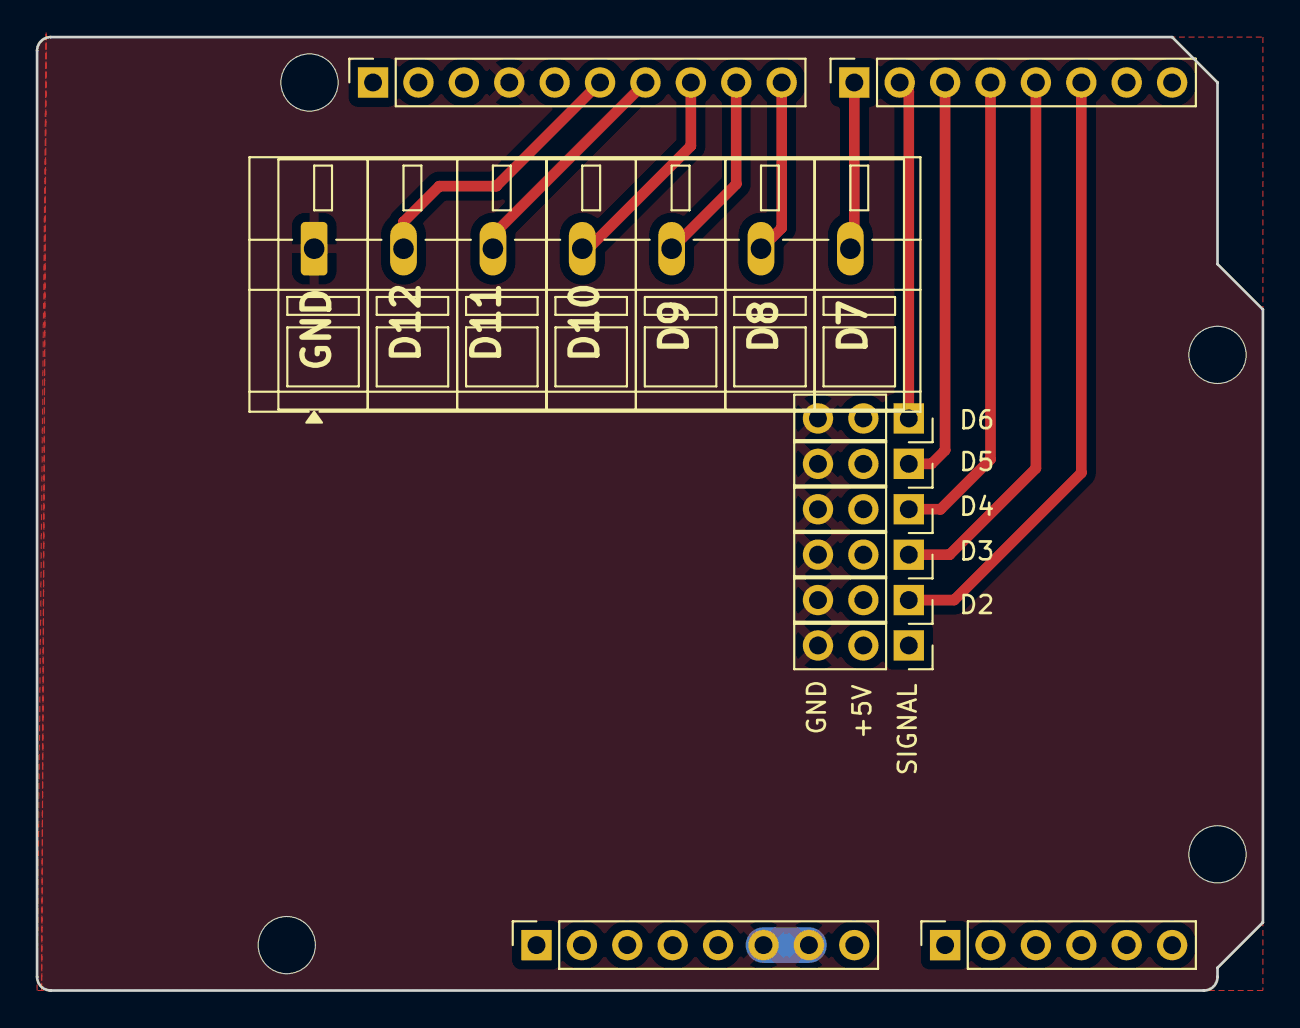
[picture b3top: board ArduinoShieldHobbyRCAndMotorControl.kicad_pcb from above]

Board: 2 copper layers, 68.6 x 53.3 mm, 15 parts (0 on the bottom side), 13 nets.

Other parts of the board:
MH1, MH2, MH3, MH4: MountingHole_3.2mm

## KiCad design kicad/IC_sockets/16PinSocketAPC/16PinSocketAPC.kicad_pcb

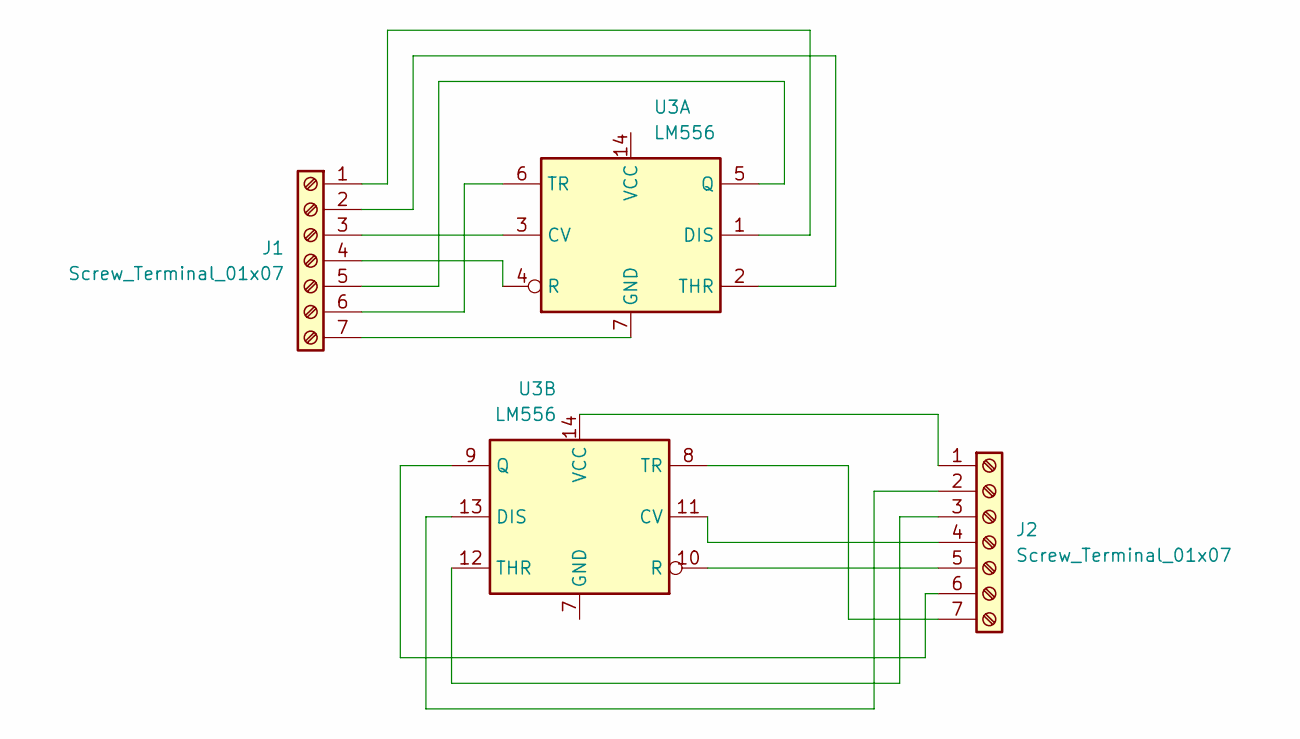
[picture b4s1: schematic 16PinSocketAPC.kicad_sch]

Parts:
J1, J2: Screw_Terminal_01x07; TerminalBlock_Phoenix_MKDS-1,5-7-5.08_1x07_P5.08mm_Horizont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
U3: LM556; DIP-14_W7.62mm_Socket_LongPads

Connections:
unnamed: J1.1, U3.1 (DIS)
unnamed: J1.2, U3.2 (THR)
unnamed: J1.3, U3.3 (CV)
unnamed: J1.4, U3.4 (R)
unnamed: J1.5, U3.5 (Q)
unnamed: J1.6, U3.6 (TR)
unnamed: J1.7, U3.7 (GND)
unnamed: J2.1, U3.14 (VCC)
unnamed: J2.2, U3.13 (DIS)
unnamed: J2.3, U3.12 (THR)
unnamed: J2.4, U3.11 (CV)
unnamed: J2.5, U3.10 (R)
unnamed: J2.6, U3.9 (Q)
unnamed: J2.7, U3.8 (TR)

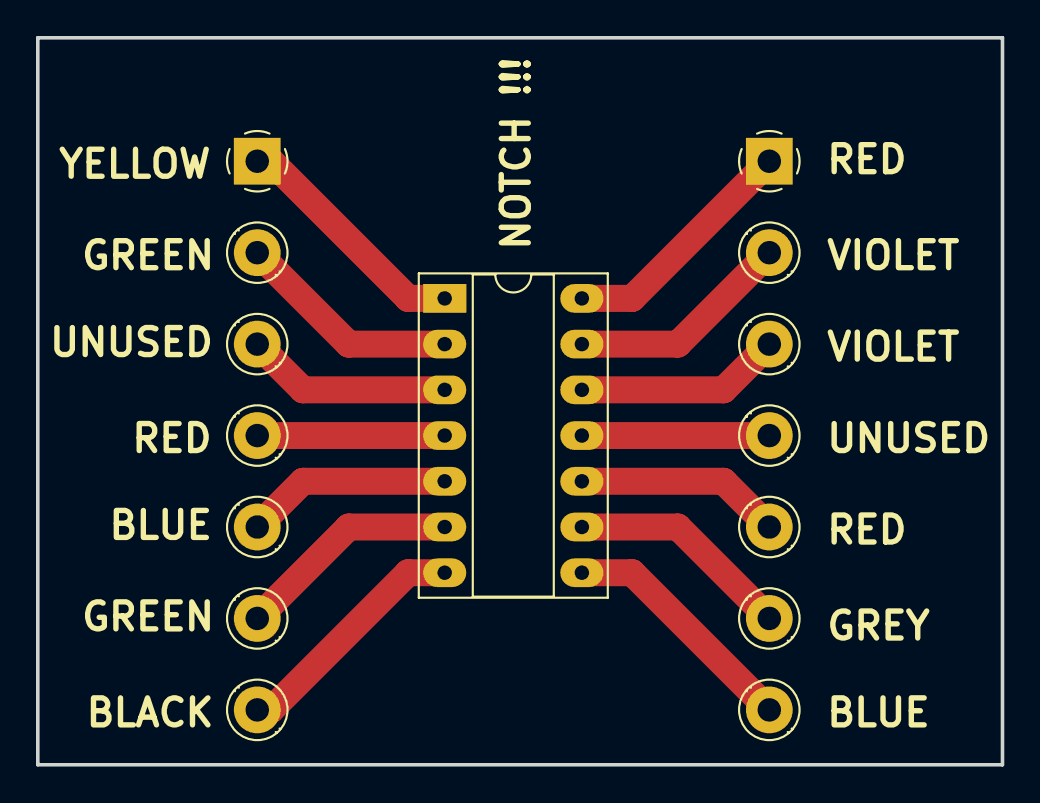
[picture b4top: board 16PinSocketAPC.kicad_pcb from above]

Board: 2 copper layers, 53.6 x 40.4 mm, 3 parts (0 on the bottom side), 14 nets.

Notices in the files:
kicad/ArduinoShieldHobbyRCAndMotorControl/ArduinoShieldHobbyRCAndMotorControl.kicad_pcb:
GPLv3 License Applies
kicad/arduinoMegaServoShield/arduinoMegaServoShield.kicad_pcb:
GPLv3 Applies
